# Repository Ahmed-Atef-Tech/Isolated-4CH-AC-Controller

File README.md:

# Isolated-4CH-AC-Controller

**ISO-AC4-FB:** A 4-Channel isolated AC controller (220V/8A) engineered in KiCad. Designed for high reliability with Solid State Relays (SSRs), active AC feedback, 1oz copper traces, and strict safety isolation routing.

---

##  Uncompromising Safety Features

Designing a mixed-signal board that handles 220V AC alongside 5V DC logic demands strict adherence to safety standards. This board incorporates multiple layers of electrical and physical protection to ensure user safety and device longevity:

* **Transient Surge Protection (MOV):** A 10D431K Varistor is placed in parallel with the main AC input to absorb damaging voltage spikes and transients from the mains supply, protecting the downstream SSRs and loads.
* **Individual Channel Overcurrent Protection:** Instead of relying on a single main fuse, each of the 4 output channels is individually protected by a dedicated fuse. This ensures that a short circuit or overload on one specific load will safely blow its respective fuse without shutting down the entire system or damaging the SSR.
* **Physical Isolation Slots (Creepage Enhancement):** To completely eliminate the risk of high-voltage arcing across the PCB surface, 1.0mm milled isolation slots were routed between the high-voltage (AC) and low-voltage (DC) zones. This physically converts the creepage distance into clearance, vastly exceeding standard safety requirements.
* **Silkscreen Safety Demarcation:** For safe handling and maintenance, the AC high-voltage region is explicitly demarcated on the silkscreen layer with clear boundary lines and "DANGER / HIGH VOLTAGE" warnings. This visual barrier prevents accidental contact by technicians during assembly or testing.

---

##  Component Highlight: Why Omron G3MB SSRs?

For the switching mechanism, traditional Electro-Mechanical Relays (EMRs) and discrete TRIAC circuits were intentionally avoided in favor of the **Omron G3MB Series Solid State Relays (SSRs)**. This selection provides several massive engineering advantages:

* **Integrated Zero-Cross Circuitry:** By utilizing the zero-cross models (e.g., G3MB-202P / PEG), the SSR only switches the load when the AC sine wave crosses 0V. This eliminates destructive arcing, prevents massive inrush currents, and completely removes the need to design a complex external zero-crossing detection circuit.
* **Built-in RC Snubber:** The relay features an internal snubber circuit that absorbs sudden voltage spikes (dv/dt) typically generated by inductive loads. This provides robust protection without requiring external capacitors and resistors.
* **Ultra-Compact Footprint (SIP-4):** The vertical Single In-line Package takes up a fraction of the PCB space compared to bulky mechanical relays, which was crucial for fitting 4 fully isolated AC channels on a single compact board.
* **Silent Operation & Infinite Lifespan:** As a semiconductor device with no moving parts, the SSR operates in absolute silence (a mandatory requirement for smart home automation) and is immune to mechanical wear, contact degradation, or welding, guaranteeing a virtually infinite lifespan.
* **Low Drive Current:** The internal LED requires extremely low trigger current (~10-20mA at 5V). This allows the SSRs to be driven directly by standard logic-level signals, completely eliminating the need for external BJT driving transistors and flyback diodes.

---

##  How the Active AC Feedback Works

Unlike standard relay boards that blindly send a control signal without knowing the actual state of the load, this board actively monitors the AC output to verify that power is successfully reaching the terminal. 

The feedback loop operates through a secure, 4-step hardware process:

1. **Voltage Sampling:** When the SSR turns on and 220V AC is present at the output terminal, a minuscule sample current (~2mA) is tapped through high-value current-limiting resistors (e.g., 47kΩ).
2. **Optical Isolation:** This sample current drives the internal bidirectional LEDs of an **LTV-814 AC Optocoupler**. This guarantees absolute galvanic isolation—transferring the status signal via light while keeping the 220V mains completely separated from the 5V logic side.
3. **Signal Conditioning:** Because the 50Hz AC mains crosses zero 100 times per second, the optocoupler's transistor output inherently pulses. To prevent erratic MCU readings, a **10uF smoothing capacitor** paired with a 10kΩ pull-down resistor acts as a low-pass filter, converting the pulsed output into a clean, stable DC logic level.
4. **MCU Logic Verification:** 
   * **State HIGH (5V):** The MCU reads a solid HIGH, confirming the load is actively powered.
   * **State LOW (0V):** The MCU reads LOW, instantly indicating that the SSR is off, the channel's fuse has blown, or there is a total mains power failure.

---

##  Known Limitations and Proposed Revisions (Rev 2.0)

**1. AC Routing Topology & Isolation Constraints**
* **Current Implementation:** Due to strict board size constraints in this initial prototype, the 220V `AC_N` line (used strictly for low-current voltage sensing/feedback) and the 5V `VCC` logic line were routed using a Daisy-Chain topology. Trace widths were set to 0.5mm, which is electrically sufficient for the minimal control current (~10mA).
* **Engineering Assessment:** While the current capacity is well within safe margins for a 1oz copper board, the daisy-chain approach in the high-voltage section makes it difficult to maintain optimal IPC-2221 clearance distances. Relying solely on soldermask for high-voltage separation is not ideal for long-term industrial reliability.
* **Action Plan for Production (Rev 2.0):** The next revision will transition the high-voltage routing to a **Star Topology** directly from the input terminal. Furthermore, isolation milling slots will be implemented between the interconnected AC nodes to strictly enforce standard creepage distances.

**2. Wireless Connectivity & IoT Integration**
* **Action Plan for Rev 2.0:** The current prototype relies on an external microcontroller connected via pin headers. In the next revision, the component placement and routing will be heavily optimized to include a dedicated socket for an **ESP-01 module** (or a fully integrated **ESP8266/ESP32** circuit). This will allow the PCB to act as a standalone, plug-and-play IoT shield, enabling seamless Wi-Fi control and smart home integration right out of the box without any external wiring.

**3. Mechanical Design & Productization**
* **Action Plan for Rev 2.0:** To bridge the gap between a bare PCB and a consumer-ready device, a custom **3D-printable enclosure** will be designed. This will provide a professional aesthetic, ensure secure mounting, and most importantly, guarantee physical isolation and safety from high-voltage AC contacts for the end-user.

**4. Schematic Refactoring & Annotation Optimization**
* **Action Plan for Rev 2.0:** The schematic diagram will be completely refactored to enhance readability and logical flow. Component designators will be systematically re-annotated and grouped by functional blocks (e.g., sequentially per channel). This structured approach will significantly simplify troubleshooting, improve the BOM organization, and streamline the overall PCB assembly process.

---

##  BOM Corrections (Important)

Please note the following two assembly corrections regarding the current `.kicad_sch` labels:

1. **Fuses (F1-F4):** The schematic shows **2.5A**, but the SSR max limit is 2A. You **MUST use 1.5A or 2A Fast-Acting fuses** to safely protect the relays from overload.
2. **SSR Model:** The schematic lists `G3MB-202PL` (Random-ON). To leverage the Zero-Cross switching and EMI reduction features, you must install the **`G3MB-202P`** or **`G3MB-202PEG`** (with built-in snubber) variants instead.

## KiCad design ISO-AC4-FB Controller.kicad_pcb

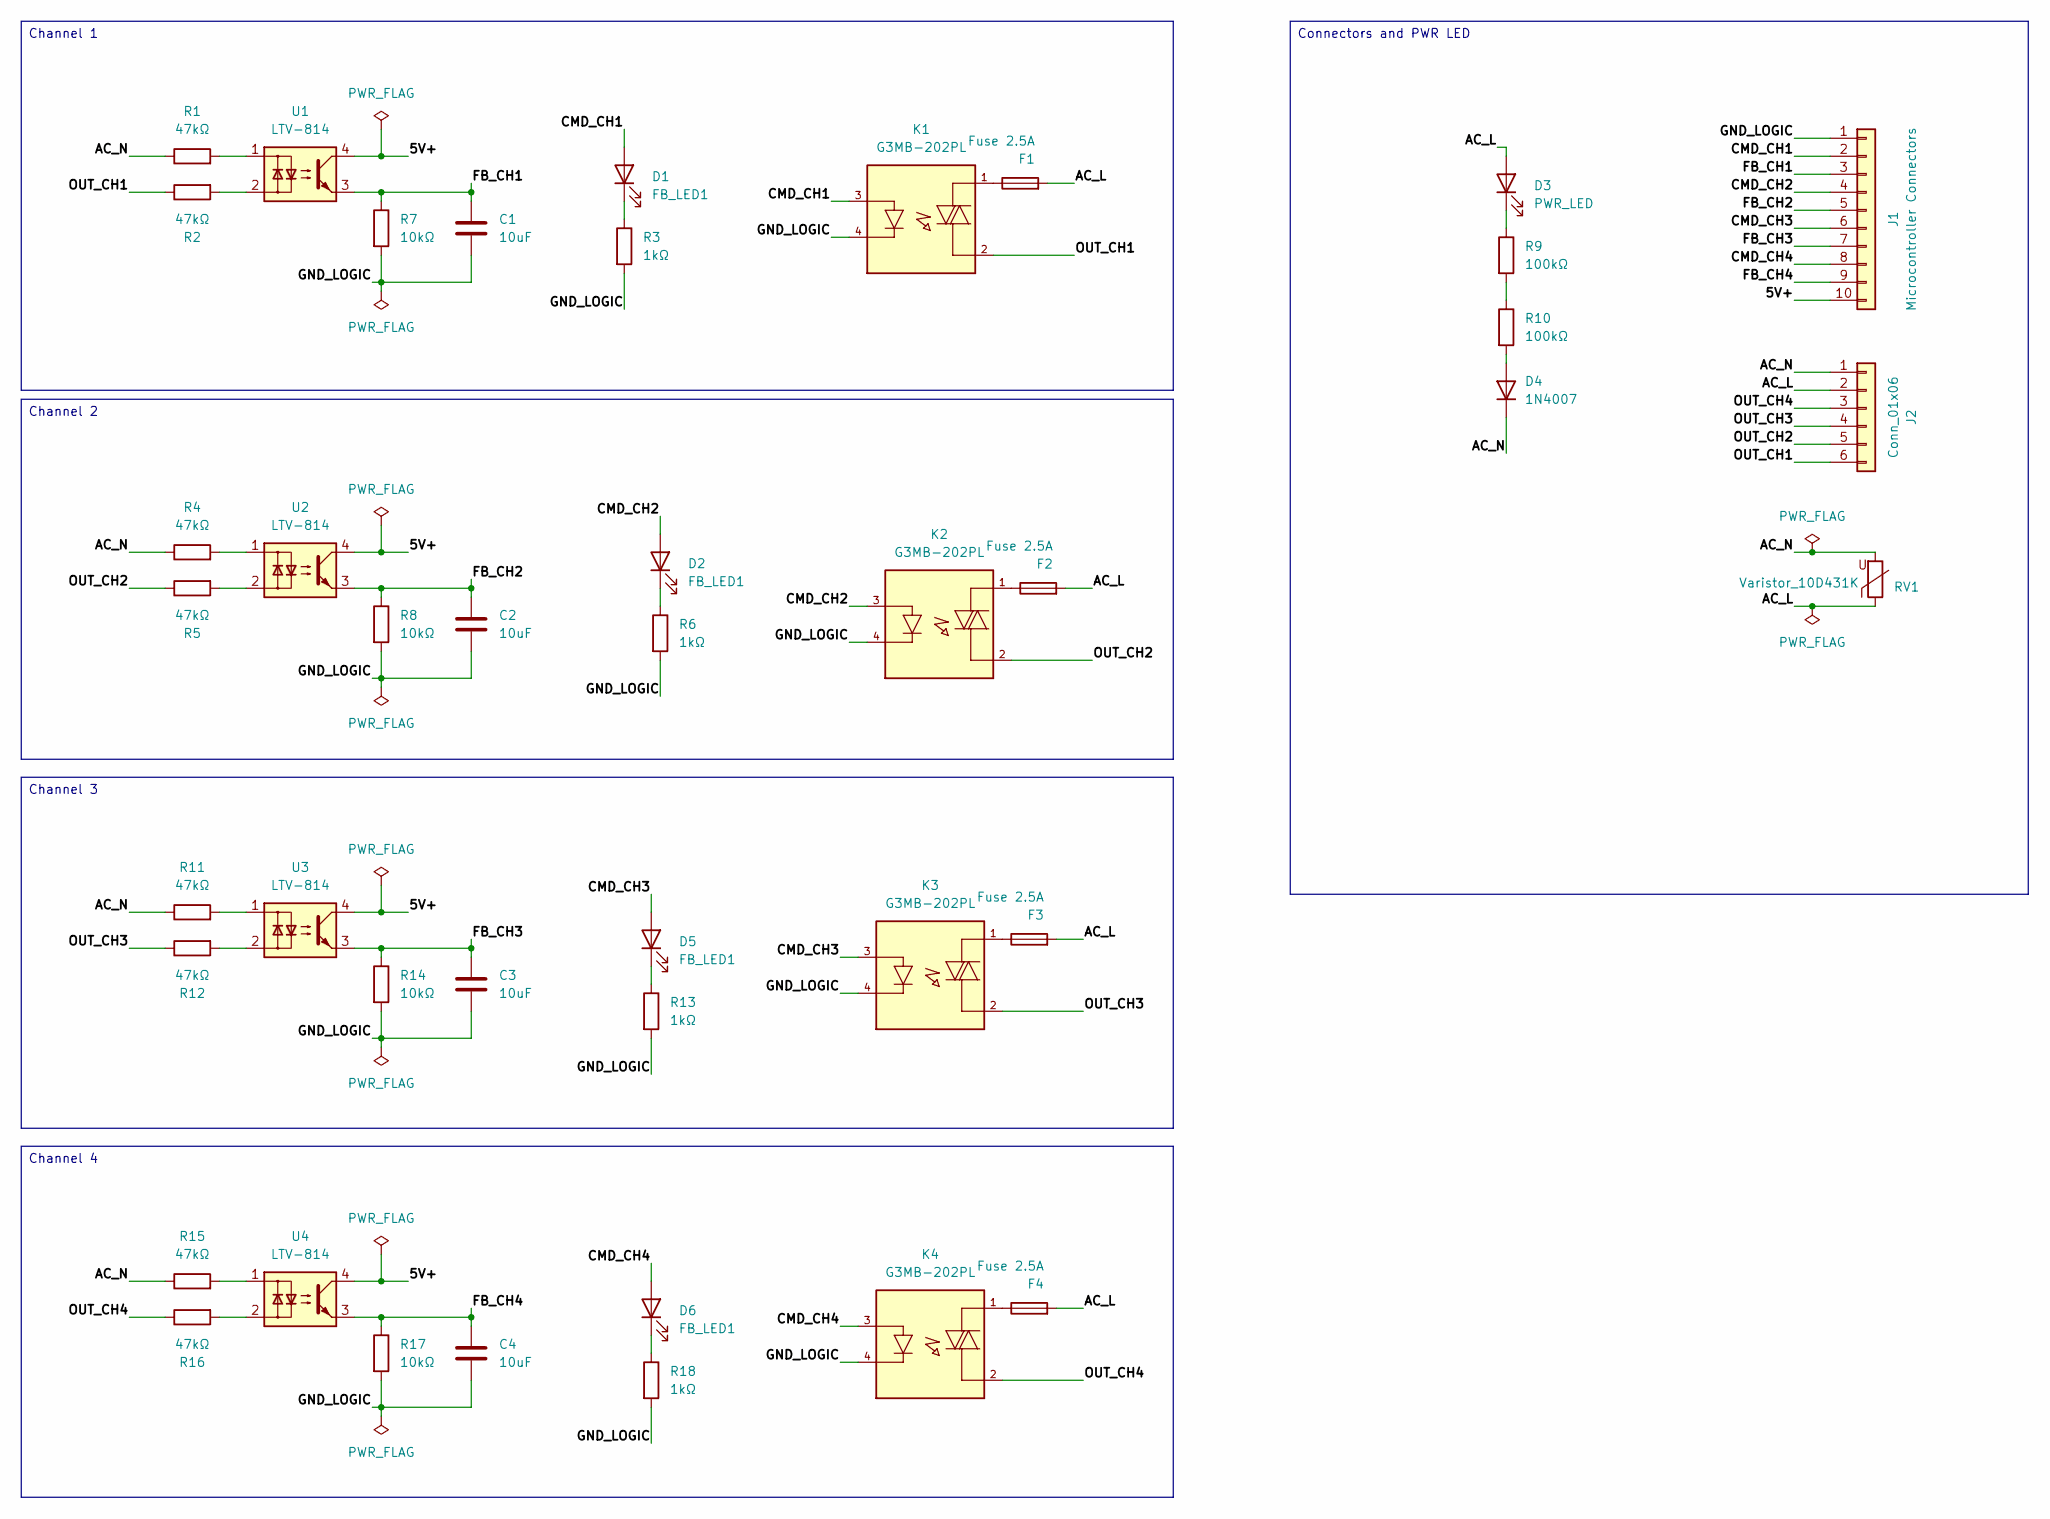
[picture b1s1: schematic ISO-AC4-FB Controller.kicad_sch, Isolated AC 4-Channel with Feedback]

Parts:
C1, C2, C3, C4: 10uF; C_1206_3216Metric
D1, D2, D5, D6: FB_LED1; LED_1206_3216Metric
D3: PWR_LED; LED_1206_3216Metric
D4: 1N4007; D_SMA
F1, F2, F3, F4: Fuse 2.5A; FUSE_36911000000
J1: Microcontroller Connectors; PinHeader_1x10_P2.54mm_Vertical
J2: Conn_01x06; TerminalBlock_Phoenix_MKDS-3-6-5.08_1x06_P5.08mm_Horizontal
K1, K2, K3, K4: G3MB-202PL; RELAY_G3MB-202P_DC12; PARTREV 06/09
R1, R2, R4, R5, R11, R12, R15, R16: 47kΩ; R_2512_6332Metric
R3, R6, R13, R18: 1kΩ; R_1206_3216Metric
R7, R8, R14, R17: 10kΩ; R_1206_3216Metric
R9, R10: 100kΩ; R_1206_3216Metric
RV1: Varistor_10D431K; RV_Disc_D12mm_W4mm_P7.5mm
U1, U2, U3, U4: LTV-814; DIP-4_W7.62mm

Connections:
/5V+: J1.10, U1.4, U2.4, U3.4, U4.4
/AC_L: D3.2 (A), F1.2, F2.2, F3.2, F4.2, J2.2, RV1.1
/AC_N: D4.1 (K), J2.1, R1.1, R4.1, R11.1, R15.1, RV1.2
/CMD_CH1: D1.2 (A), J1.2, K1.3
/CMD_CH2: D2.2 (A), J1.4, K2.3
/CMD_CH3: D5.2 (A), J1.6, K3.3
/CMD_CH4: D6.2 (A), J1.8, K4.3
/FB_CH1: C1.1, J1.3, R7.1, U1.3
/FB_CH2: C2.1, J1.5, R8.1, U2.3
/FB_CH3: C3.1, J1.7, R14.1, U3.3
/FB_CH4: C4.1, J1.9, R17.1, U4.3
/GND_LOGIC: C1.2, C2.2, C3.2, C4.2, J1.1, K1.4, K2.4, K3.4, K4.4, R3.2, R6.2, R7.2, R8.2, R13.2, R14.2, R17.2, R18.2
/OUT_CH1: J2.6, K1.2, R2.1
/OUT_CH2: J2.5, K2.2, R5.1
/OUT_CH3: J2.4, K3.2, R12.1
/OUT_CH4: J2.3, K4.2, R16.1
unnamed: D1.1 (K), R3.1
unnamed: D2.1 (K), R6.1
unnamed: D3.1 (K), R9.1
unnamed: D4.2 (A), R10.2
unnamed: D5.1 (K), R13.1
unnamed: D6.1 (K), R18.1
unnamed: F1.1, K1.1
unnamed: F2.1, K2.1
unnamed: F3.1, K3.1
unnamed: F4.1, K4.1
unnamed: R1.2, U1.1
unnamed: R2.2, U1.2
unnamed: R4.2, U2.1
unnamed: R5.2, U2.2
unnamed: R9.2, R10.1
unnamed: R11.2, U3.1
unnamed: R12.2, U3.2
unnamed: R15.2, U4.1
unnamed: R16.2, U4.2

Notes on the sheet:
Channel 4
Channel 3
Connectors and PWR LED
Channel 2
Channel 1

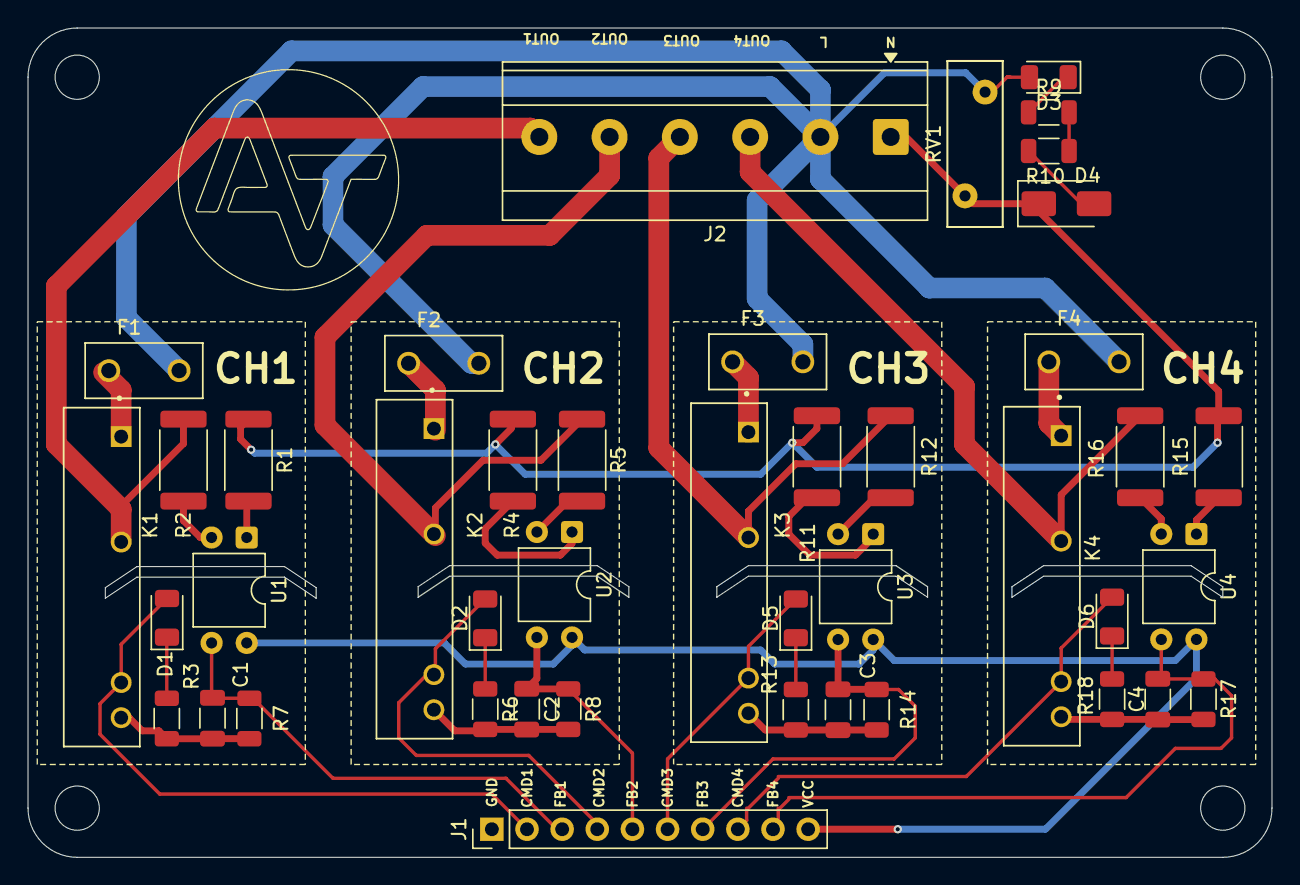
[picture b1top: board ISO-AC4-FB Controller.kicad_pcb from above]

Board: 2 copper layers, 89.9 x 59.9 mm, 43 parts (0 on the bottom side), 35 nets.

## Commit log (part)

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2026-04-27 Files Upload
